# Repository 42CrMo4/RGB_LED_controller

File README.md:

# KiCad_Template

Controll RGB LED Strips with an ATTINY

[Bill of Material](Fabrication/BoM/design-bom-short.csv)

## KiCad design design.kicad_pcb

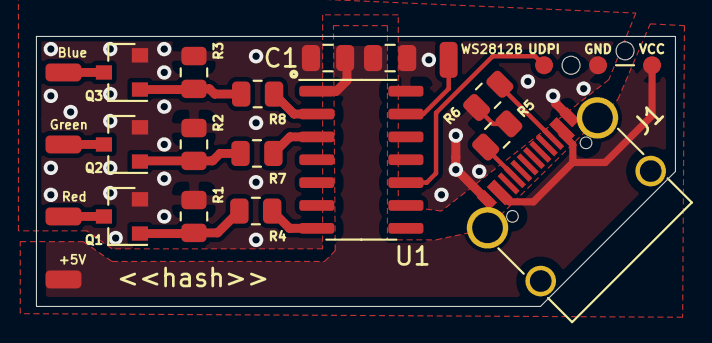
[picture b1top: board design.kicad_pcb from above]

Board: 2 copper layers, 35.5 x 15.0 mm, 21 parts (0 on the bottom side), 15 nets.

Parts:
C1: 10nF; C_0805_2012Metric
C2: 100nF / 0.1uF; C_0805_2012Metric
J1: HRO_TYPE-C-31-M-12; USB_C_Receptacle_HRO_TYPE-C-31-M-12_simple
J2: UDPI-connector; UDPI_interface_small
Q1, Q2, Q3: a2shb; SOT-23
R1, R2, R3: 300k; R_0805_2012Metric
R4, R7, R8: 100; R_0805_2012Metric
R5, R6: 5.1k; R_0805_2012Metric
TP1: Red-; SolderWirePad_1x01_SMD_1x2mm
TP2: Grenn-; SolderWirePad_1x01_SMD_1x2mm
TP3: Blue-; SolderWirePad_1x01_SMD_1x2mm
TP4: WS2812B; SolderWirePad_1x01_SMD_1x2mm
TP5: VCC; SolderWirePad_1x01_SMD_1x2mm
U1: ATtiny814-SS; SOIC-14_3.9x8.7mm_P1.27mm

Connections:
Blue_PWM: R8.1, U1.2
Blue_neg: Q3.3, TP3.1
GND: C1.2, C2.2, J1.A1, J1.A12, J1.B1, J1.B12, J1.S1, J2.3, Q1.2, Q2.2, Q3.2, R1.2, R2.2, R3.2, R5.2, R6.2, U1.14
Green_PWM: R7.1, U1.3
Green_neg: Q2.3, TP2.1
unnamed: J1.A5, R5.1
unnamed: J1.B5, R6.1
unnamed: Q1.1, R1.1, R4.2
unnamed: Q2.1, R2.1, R7.2
unnamed: Q3.1, R3.1, R8.2
Red_PWM: R4.1, U1.7
Red_neg: Q1.3, TP1.1
UDPI: J2.1, U1.10
VCC: C1.1, C2.1, J1.A4, J1.A9, J1.B4, J1.B9, J2.2, TP5.1, U1.1
WS2812b: TP4.1, U1.13

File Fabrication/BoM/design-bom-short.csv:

Row,Description,Part,References,Value,Footprint,Quantity Per PCB,Status,Datasheet
1,"Unpolarized capacitor, small symbol",C_Small,C1,10nF,C_0805_2012Metric,1, ,~
2,"Unpolarized capacitor, small symbol",C_Small,C2,100nF / 0.1uF,C_0805_2012Metric,1, ,~
3,USB Full-Featured Type-C Receptacle connector,USB_C_Receptacle,J1,HRO_TYPE-C-31-M-12,USB_C_Receptacle_HRO_TYPE-C-31-M-12_simple,1, ,https://www.usb.org/sites/default/files/documents/usb_type-c.zip
4,"Generic connector, single row, 01x05, script generated (kicad-library-utils/schlib/autogen/connector/)",Conn_01x05,J2,UDPI-connector,UDPI_interface_small,1, ,~
5,"0.38A Id, 60V Vds, N-Channel MOSFET, SOT-23",2N7002K,Q1 Q2 Q3,a2shb,SOT-23,3, ,https://www.diodes.com/assets/Datasheets/ds30896.pdf
6,"Resistor, small symbol",R_Small,R4 R7 R8,100,R_0805_2012Metric,3, ,~
7,"Resistor, small symbol",R_Small,R5 R6,5.1k,R_0805_2012Metric,2, ,~
8,"Resistor, small symbol",R_Small,R1 R2 R3,300k,R_0805_2012Metric,3, ,~
9,"20MHz, 8kB Flash, 512B SRAM, 128B EEPROM, SOIC-14",ATtiny814-SS,U1,ATtiny814-SS,SOIC-14_3.9x8.7mm_P1.27mm,1, ,http://ww1.microchip.com/downloads/en/DeviceDoc/40001912A.pdf

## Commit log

2021-10-24 add gitignore / workflows
2021-10-24 Update Bom
2021-10-24 move hash
2021-11-30 add components
    usb resistor cc, power flags, mosfet gate resistor
2021-11-30 simple usb c footprint
2021-11-30 PCB: arranged components
2021-11-30 test move
2021-11-30 Revert "test move"
    This reverts commit 2e1d361661dc7598fb9903e984668c57044029d5.
2021-11-30 Revert "Update Bom"
    This reverts commit cf23068970612d945d65626055d6b80e3e3875a1.
2021-11-30 Revert "PCB: arranged components"
    This reverts commit c075e54a899e95ed4df332e44d0b53e3f67b4dca.
2021-11-30 Revert "simple usb c footprint"
    This reverts commit 12942baa332d339e718c995e44cede0abfa1d6b5.
2021-11-30 Revert "add components"
    This reverts commit 60fcf040a8541399063354e6f95bf0141af0d636.
2021-11-30 Revert "PCB: arranged components"
    This reverts commit 1e630d8c129b64ed8c836ca474e6fbe4f1a6a721.
2021-11-30 PCB: change usb footprint add components
2021-11-30 PCB: move components
2021-11-30 PCB: arrange
2021-11-30 PCB: text and hide unused annotation
2021-11-30 PCB: added USB 3D model
2021-12-01 SCH: added +5V Pad
2021-12-01 PCB: add 5V, rotate USB-C
2021-12-01 PCB: update udpi footprint
    GND in middle
2021-12-01 SCH: Annotation
2021-12-01 SCH: change 5V to VCC Label
2021-12-01 PRO: added 0.5mm trace
2021-12-01 PRO: add 0.4 trace size
2021-12-01 PCB: routing
2021-12-01 PCB: refinement
2021-12-03 PCB: added GND Vias
2021-12-03 PCB: changed VCC plane
2021-12-03 PCB: refined GND plane
2021-12-03 PCB: changes due to DRC
2021-12-03 SCH: added values
2021-12-03 PCB: change Fill on power path to solid
2021-12-03 PCB: addapt VCC plane
2021-12-05 PCB: refinement for Aisler
2021-12-05 PCB: add PIN1 dot U1
2021-12-16 SW: initial
2021-12-17 SW: change output pin to PB2
    PinPB3 is not PWM capable
2021-12-17 SCH: change pin PB3 to PB2 for Red LED
    PinPB3 is not PMW capable
2021-12-17 PCB: change Red LED output to PB2
    PinPB3 is not PMW capable
2021-12-17 lower fadeamount and delay
2021-12-17 SW: formating
2021-12-17 add ToDo list
